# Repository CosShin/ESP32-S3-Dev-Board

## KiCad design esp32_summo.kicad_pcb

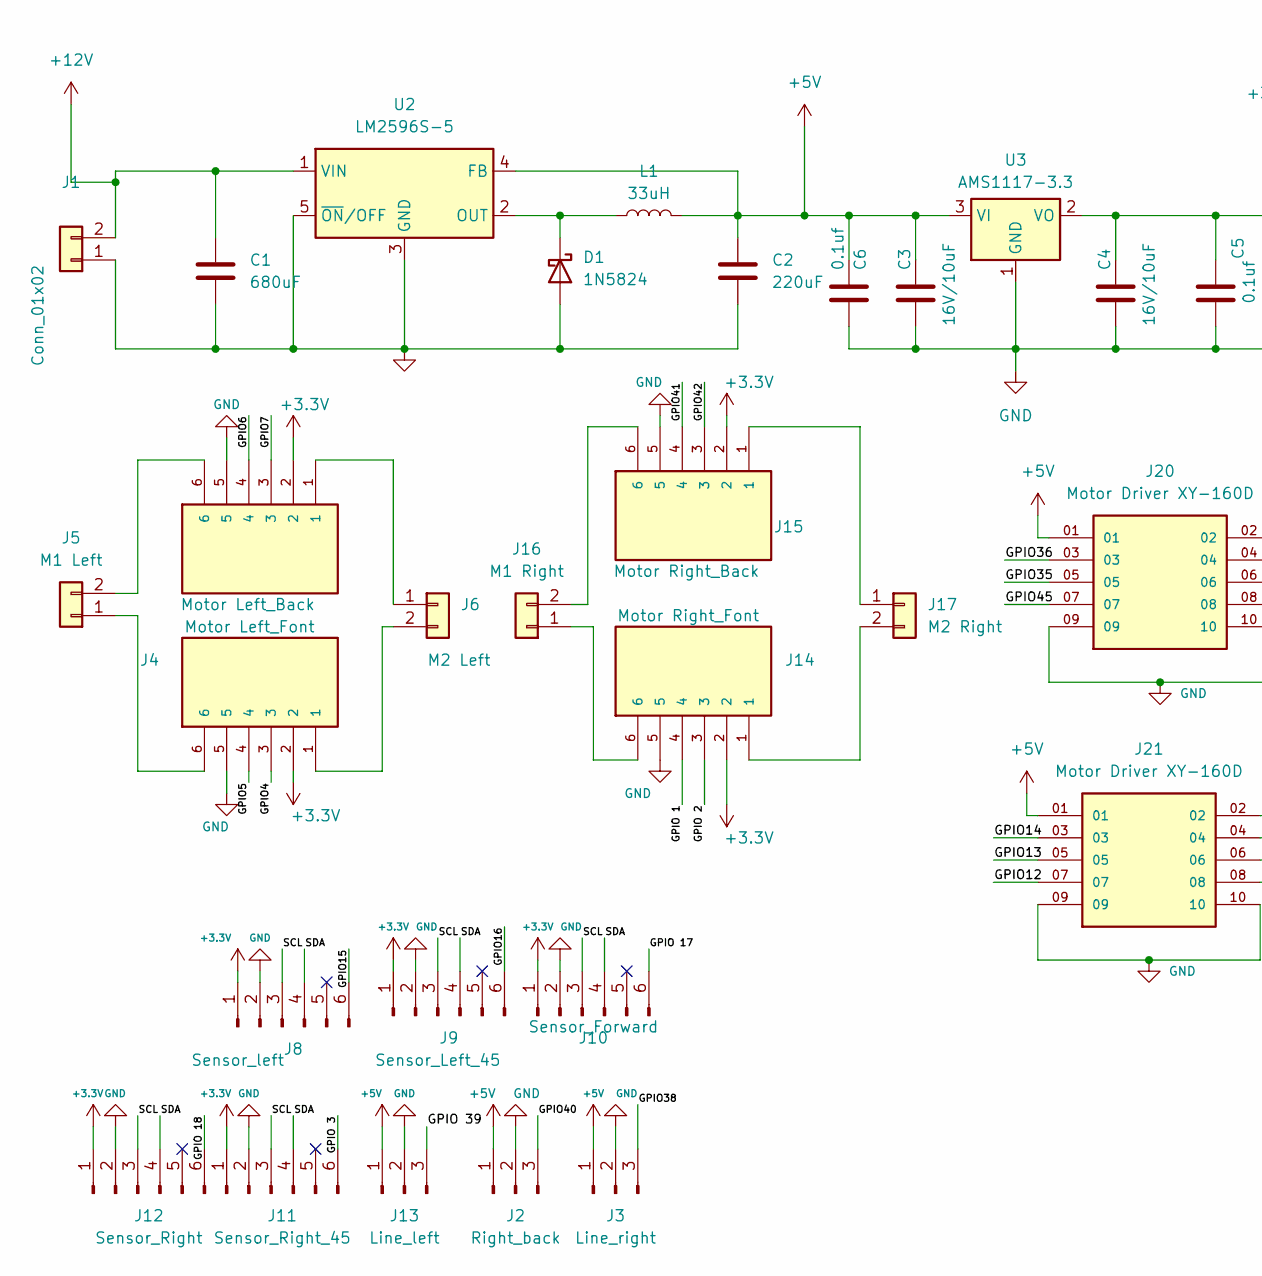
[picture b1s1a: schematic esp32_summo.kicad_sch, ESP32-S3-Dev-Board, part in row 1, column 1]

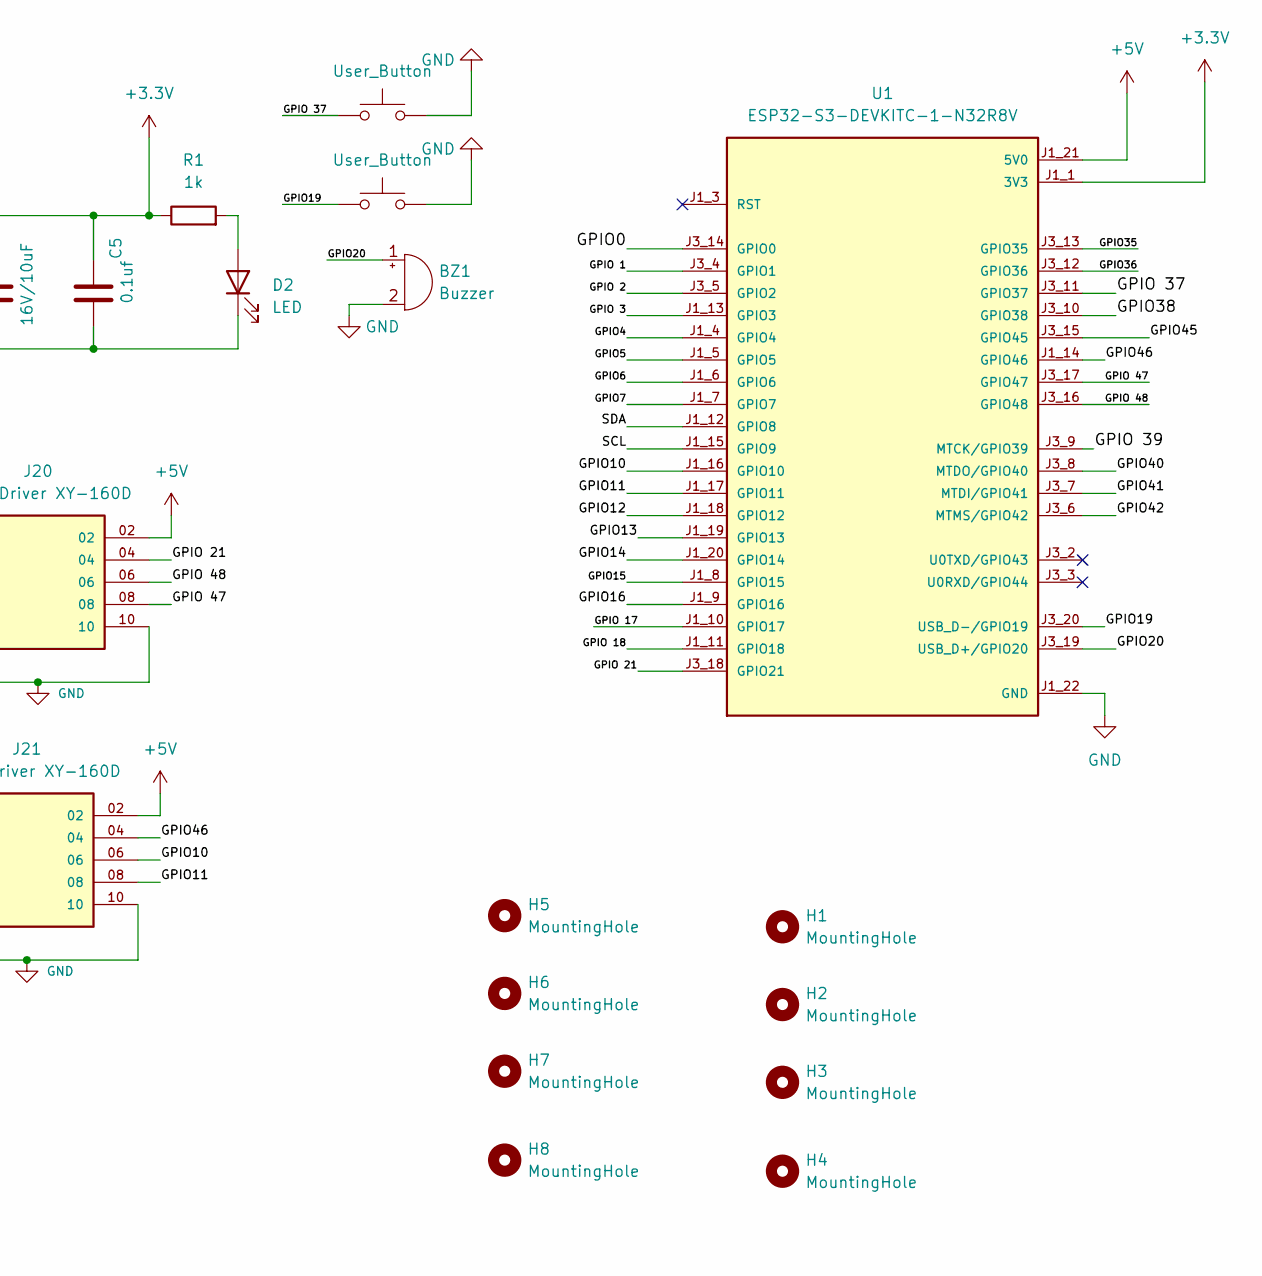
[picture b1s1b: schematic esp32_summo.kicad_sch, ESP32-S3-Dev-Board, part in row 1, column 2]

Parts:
BZ1: Buzzer; Buzzer_12x9.5RM7.6
C1: 680uF; CP_Radial_D10.0mm_P5.00mm
C2: 220uF; CP_Radial_D6.3mm_P2.50mm
C3, C4: 16V/10uF; CP_Radial_D4.0mm_P1.50mm
C5, C6: 0.1uf; CP_Radial_D4.0mm_P1.50mm
D1: 1N5824; D_DO-201AD_P15.24mm_Horizontal
D2: LED; LED_D5.0mm
H1, H2, H3, H4, H5, H6, H7, H8: MountingHole; MountingHole_3.2mm_M3
J1: Conn_01x02; TE_282837-2
J2: Right_back; JST_EH_B3B-EH-A_1x03_P2.50mm_Vertical
J3: Line_right; JST_EH_B3B-EH-A_1x03_P2.50mm_Vertical
J4: Motor Left_Font; JST_PH_B6B-PH-K_1x06_P2.00mm_Vertical; PARTREV N/A
J5: M1 Left; TE_282837-2
J6: M2 Left; TE_282837-2
J7: Motor Left_Back; JST_PH_B6B-PH-K_1x06_P2.00mm_Vertical; PARTREV N/A
J8: Sensor_left; JST_EH_B6B-EH-A_1x06_P2.50mm_Vertical
J9: Sensor_Left_45; JST_EH_B6B-EH-A_1x06_P2.50mm_Vertical
J10: Sensor_Forward; JST_EH_B6B-EH-A_1x06_P2.50mm_Vertical
J11: Sensor_Right_45; JST_EH_B6B-EH-A_1x06_P2.50mm_Vertical
J12: Sensor_Right; JST_EH_B6B-EH-A_1x06_P2.50mm_Vertical
J13: Line_left; JST_EH_B3B-EH-A_1x03_P2.50mm_Vertical
J14: Motor Right_Font; JST_PH_B6B-PH-K_1x06_P2.00mm_Vertical; PARTREV N/A
J15: Motor Right_Back; JST_PH_B6B-PH-K_1x06_P2.00mm_Vertical; PARTREV N/A
J16: M1 Right; TE_282837-2
J17: M2 Right; TE_282837-2
J20, J21: Motor Driver XY-160D; SAMTEC_ZSS-105-01-S-D-480; PARTREV T
L1: 33uH; L_Radial_D12.5mm_P7.00mm_Fastron_09HCP
R1: 1k; R_Axial_DIN0207_L6.3mm_D2.5mm_P7.62mm_Horizontal
SW1, SW4: User_Button; SW_Push_1P1T_NO_CK_KSC9xxJ
U1: ESP32-S3-DEVKITC-1-N32R8V; XCVR_ESP32-S3-DEVKITC-1-N32R8V; PARTREV 1.1
U2: LM2596S-5; TO-263-5_TabPin3
U3: AMS1117-3.3; SOT-223-3_TabPin2

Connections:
+3.3V: C4.1, C5.1, J4.2, J7.2, J8.1, J9.1, J10.1, J11.1, J12.1, J14.2, J15.2, R1.1, U1.J1_1 (3V3), U1.J1_2 (3V3), U3.2 (VO)
+5V: C2.1, C3.1, C6.1, J2.1, J3.1, J13.1, J20.01, J20.02, J21.01, J21.02, L1.2, U1.J1_21 (5V0), U2.4 (FB), U3.3 (VI)
+12V: C1.1, J1.2, U2.1 (VIN)
/GPIO0: U1.J3_14 (GPIO0)
/GPIO4: J4.3, U1.J1_4 (GPIO4)
/GPIO5: J4.4, U1.J1_5 (GPIO5)
/GPIO6: J7.4, U1.J1_6 (GPIO6)
/GPIO7: J7.3, U1.J1_7 (GPIO7)
/GPIO10: J21.06, U1.J1_16 (GPIO10)
/GPIO11: J21.08, U1.J1_17 (GPIO11)
/GPIO12: J21.07, U1.J1_18 (GPIO12)
/GPIO13: J21.05, U1.J1_19 (GPIO13)
/GPIO14: J21.03, U1.J1_20 (GPIO14)
/GPIO15: J8.6, U1.J1_8 (GPIO15)
/GPIO16: J9.6, U1.J1_9 (GPIO16)
/GPIO19: SW1.1, U1.J3_20 (USB_D-/GPIO19)
/GPIO20: BZ1.1 (+), U1.J3_19 (USB_D+/GPIO20)
/GPIO35: J20.05, U1.J3_13 (GPIO35)
/GPIO36: J20.03, U1.J3_12 (GPIO36)
/GPIO38: J3.3, U1.J3_10 (GPIO38)
/GPIO40: J2.3, U1.J3_8 (MTDO/GPIO40)
/GPIO41: J15.4, U1.J3_7 (MTDI/GPIO41)
/GPIO42: J15.3, U1.J3_6 (MTMS/GPIO42)
/GPIO45: J20.07, U1.J3_15 (GPIO45)
/GPIO46: J21.04, U1.J1_14 (GPIO46)
/GPIO 1: J14.4, U1.J3_4 (GPIO1)
/GPIO 2: J14.3, U1.J3_5 (GPIO2)
/GPIO 3: J11.6, U1.J1_13 (GPIO3)
/GPIO 17: J10.6, U1.J1_10 (GPIO17)
/GPIO 18: J12.6, U1.J1_11 (GPIO18)
/GPIO 21: J20.04, U1.J3_18 (GPIO21)
/GPIO 37: SW4.1, U1.J3_11 (GPIO37)
/GPIO 39: J13.3, U1.J3_9 (MTCK/GPIO39)
/GPIO 47: J20.08, U1.J3_17 (GPIO47)
/GPIO 48: J20.06, U1.J3_16 (GPIO48)
/SCL: J8.3, J9.3, J10.3, J11.3, J12.3, U1.J1_15 (GPIO9)
/SDA: J8.4, J9.4, J10.4, J11.4, J12.4, U1.J1_12 (GPIO8)
GND: BZ1.2 (-), C1.2, C2.2, C3.2, C4.2, C5.2, C6.2, D1.2 (A), D2.1 (K), J1.1, J2.2, J3.2, J4.5, J7.5, J8.2, J9.2, J10.2, J11.2, J12.2, J13.2, J14.5, J15.5, J20.09, J20.10, J21.09, J21.10, SW1.2, SW4.2, U1.J1_22 (GND), U1.J3_1 (GND), U1.J3_21 (GND), U1.J3_22 (GND), U2.3 (GND), U2.5 (~ON/OFF), U3.1 (GND)
unnamed: D1.1 (K), L1.1, U2.2 (OUT)
unnamed: D2.2 (A), R1.2
unnamed: J4.6, J5.1
unnamed: J5.2, J7.6
unnamed: J6.1, J7.1
unnamed: J4.1, J6.2
unnamed: J14.6, J16.1
unnamed: J15.6, J16.2
unnamed: J15.1, J17.1
unnamed: J14.1, J17.2

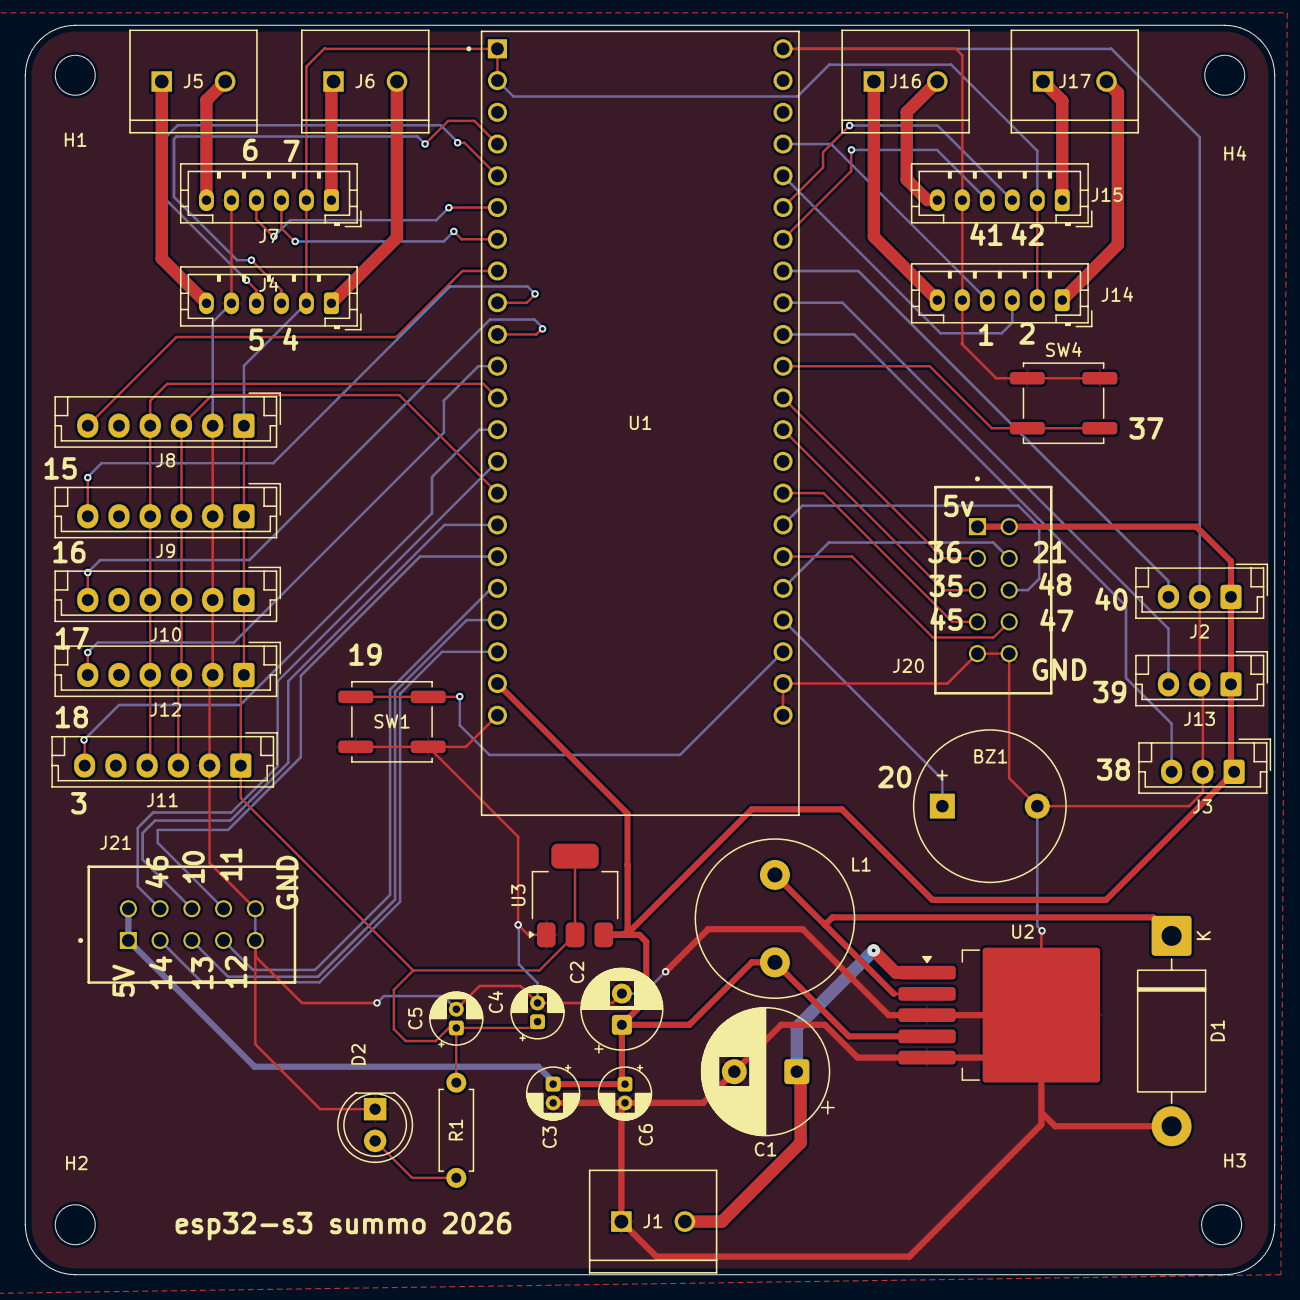
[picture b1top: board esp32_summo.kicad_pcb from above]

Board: 2 copper layers, 100.0 x 100.0 mm, 39 parts (0 on the bottom side), 47 nets.

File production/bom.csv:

Designator,Footprint,Quantity,Value,LCSC Part #
BZ1,Buzzer_12x9.5RM7.6,1,Buzzer,
C1,CP_Radial_D10.0mm_P5.00mm,1,680uF,
C2,CP_Radial_D6.3mm_P2.50mm,1,220uF,
"C3, C4",CP_Radial_D4.0mm_P1.50mm,2,16V/10uF,
"C5, C6",CP_Radial_D4.0mm_P1.50mm,2,0.1uf,
D1,D_DO-201AD_P15.24mm_Horizontal,1,1N5824,
D2,LED_D5.0mm,1,LED,
J1,TE_282837-2,1,Conn_01x02,
J10,JST_EH_B6B-EH-A_1x06_P2.50mm_Vertical,1,Sensor_Forward,
J11,JST_EH_B6B-EH-A_1x06_P2.50mm_Vertical,1,Sensor_Right_45,
J12,JST_EH_B6B-EH-A_1x06_P2.50mm_Vertical,1,Sensor_Right,
J13,JST_EH_B3B-EH-A_1x03_P2.50mm_Vertical,1,Line_left,
J14,JST_PH_B6B-PH-K_1x06_P2.00mm_Vertical,1,Motor Right_Font,
J15,JST_PH_B6B-PH-K_1x06_P2.00mm_Vertical,1,Motor Right_Back,
J16,TE_282837-2,1,M1 Right,
J17,TE_282837-2,1,M2  Right,
J2,JST_EH_B3B-EH-A_1x03_P2.50mm_Vertical,1,Right_back,
"J20, J21",SAMTEC_ZSS-105-01-S-D-480,2,Motor Driver XY-160D,
J3,JST_EH_B3B-EH-A_1x03_P2.50mm_Vertical,1,Line_right,
J4,JST_PH_B6B-PH-K_1x06_P2.00mm_Vertical,1,Motor Left_Font,
J5,TE_282837-2,1,M1 Left,
J6,TE_282837-2,1,M2 Left,
J7,JST_PH_B6B-PH-K_1x06_P2.00mm_Vertical,1,Motor Left_Back,
J8,JST_EH_B6B-EH-A_1x06_P2.50mm_Vertical,1,Sensor_left,
J9,JST_EH_B6B-EH-A_1x06_P2.50mm_Vertical,1,Sensor_Left_45,
L1,L_Radial_D12.5mm_P7.00mm_Fastron_09HCP,1,33uH,
R1,R_Axial_DIN0207_L6.3mm_D2.5mm_P7.62mm_Horizontal,1,1k,
"SW1, SW4",SW_Push_1P1T_NO_CK_KSC9xxJ,2,User_Button,
U1,XCVR_ESP32-S3-DEVKITC-1-N32R8V,1,ESP32-S3-DEVKITC-1-N32R8V,
U2,TO-263-5_TabPin3,1,LM2596S-5,
U3,SOT-223-3_TabPin2,1,AMS1117-3.3,

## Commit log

2026-03-05 Initial commit - ESP32-S3 Dev Board
